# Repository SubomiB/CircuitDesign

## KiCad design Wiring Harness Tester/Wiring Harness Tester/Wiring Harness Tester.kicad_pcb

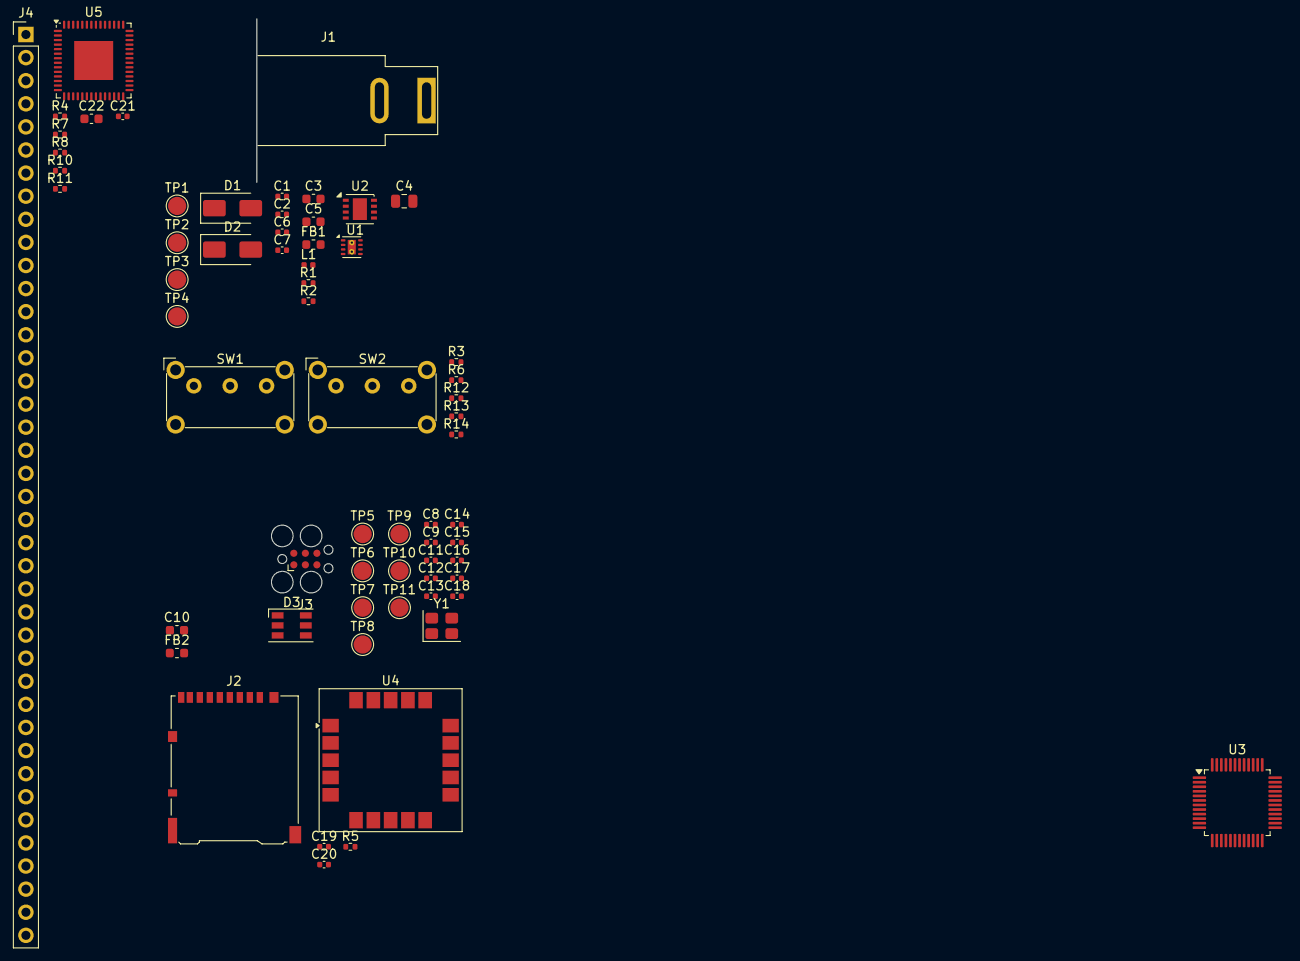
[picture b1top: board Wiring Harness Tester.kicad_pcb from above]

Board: 4 copper layers, 64 parts (0 on the bottom side), 79 nets, no tracks yet.

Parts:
C1, C2, C7, C16, C17: 1u; C_0402_1005Metric
C3: 10u; C_0603_1608Metric
C4: 22u; C_0805_2012Metric
C5, C10, C22: 4u7; C_0603_1608Metric
C6: 1n; C_0402_1005Metric
C8, C9: 10p; C_0402_1005Metric
C11, C12, C13, C14, C18, C19, C20, C21: 100n; C_0402_1005Metric
C15: 10n; C_0402_1005Metric
D1: SMAJ15A; D_SMA
D2: SS34; D_SMA
D3: CLX6F-FKC; LED_RGB_PLCC-6
FB1, FB2: 120R; L_0603_1608Metric
J1: 12V Jack; BarrelJack_SwitchcraftConxall_RAPC10U_Horizontal
J2: Micro_SD_Card_Det2; microSD_HC_Hirose_DM3AT-SF-PEJM5
J3: ST_Link; Tag-Connect_TC2030-IDC-FP_2x03_P1.27mm_Vertical
J4: Conn_01x40_Pin; PinHeader_1x40_P2.54mm_Vertical
L1: 2u2; L_0402_1005Metric
R1, R2: 100k; R_0402_1005Metric
R3, R5, R6: 10k; R_0402_1005Metric
R4, R7: 1k1; R_0402_1005Metric
R8: 2k; R_0402_1005Metric
R10, R11: 1k6; R_0402_1005Metric
R12: 75; R_0402_1005Metric
R13: 82; R_0402_1005Metric
R14: 62; R_0402_1005Metric
SW1, SW2: SW_SPDT; SW_E-Switch_EG1224_SPDT_Angled
TP1: T-GND; TestPoint_Pad_D2.0mm
TP2: T-12V; TestPoint_Pad_D2.0mm
TP3: T-5V; TestPoint_Pad_D2.0mm
TP4: T-3V3; TestPoint_Pad_D2.0mm
TP5, TP6: T-RX; TestPoint_Pad_D2.0mm
TP7: T-SCL; TestPoint_Pad_D2.0mm
TP8: T-SDA; TestPoint_Pad_D2.0mm
TP9: T-SCK; TestPoint_Pad_D2.0mm
TP10: T-MISO; TestPoint_Pad_D2.0mm
TP11: T-MOSI; TestPoint_Pad_D2.0mm
U1: TPS62163DSG; WSON-8-1EP_2x2mm_P0.5mm_EP0.9x1.6mm_ThermalVias
U2: MCP1727-3302xMF; DFN-8-1EP_3x3mm_P0.65mm_EP1.55x2.4mm
U3: STM32F103C8T6; LQFP-48_7x7mm_P0.5mm
U4: SAM-M8Q; ublox_SAM-M8Q
U5: PCA9506BS; QFN-56-1EP_8x8mm_P0.5mm_EP4.3x4.3mm
Y1: 8MHz; Crystal_SMD_3225-4Pin_3.2x2.5mm

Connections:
+3V3: C7.1, C10.1, C11.1, C12.1, C13.1, C14.1, C17.1, C19.1, C20.1, FB2.2, J2.4 (VDD), J3.1 (VCC), R2.2, R5.1, SW1.3 (C), SW2.3 (C), TP4.1, U2.7 (Sense), U2.8 (Vout), U3.1 (VBAT), U3.24 (VDD), U3.36 (VDD), U3.48 (VDD), U4.2 (VCC_IO), U4.3 (V_BCKP), U4.17 (VCC)
+5V: C4.1, C5.1, C21.1, C22.1, L1.2, R1.1, R4.1, R7.1, R8.1, R10.1, R11.1, TP3.1, U1.6 (VOS), U2.1 (Vin), U2.2 (Vin), U2.3 (~SHDN), U5.11 (V_{DD}), U5.39 (V_{DD})
+12V: C2.1, C3.1, FB1.2, TP2.1, U1.2 (VIN), U1.3 (EN)
+A3V3: C15.1, C16.1, FB2.1, U3.9 (VDDA)
/Microcontroller/SW_BOOT0: R6.1, SW2.2 (B)
BOOT0: R6.2, U3.44 (BOOT0)
Blue_LED: R12.2, U3.26 (PB13)
GND: C1.2, C2.2, C3.2, C4.2, C5.2, C6.2, C7.2, C8.2, C9.2, C10.2, C11.2, C12.2, C13.2, C14.2, C15.2, C16.2, C17.2, C18.1, C19.2, C20.2, C21.2, C22.2, D1.2 (A2), D3.1 (KB), D3.2 (KG), D3.3 (KR), J1.2, J2.6 (VSS), J2.11 (SHIELD), J3.5 (GND), SW1.1 (A), SW2.1 (A), TP1.1, U1.1 (PGND), U1.4 (AGND), U1.5 (FB), U2.4 (GND), U2.9 (GND), U3.8 (VSSA), U3.23 (VSS), U3.35 (VSS), U3.47 (VSS), U4.1 (GND), U4.4 (GND), U4.5 (GND), U4.6 (GND), U4.10 (GND), U4.11 (GND), U4.15 (GND), U4.16 (GND), U4.20 (GND), U5.4 (V_{SS}), U5.16 (V_{SS}), U5.20 (A0), U5.21 (A1), U5.22 (A2), U5.27 (V_{SS}), U5.32 (V_{SS}), U5.44 (V_{SS}), U5.55 (V_{SS}), U5.57 (V_{SS}), Y1.2, Y1.4
GPS_RESET: U3.32 (PA11), U4.18 (~RESET)
GPS_TIMEPULSE: U3.30 (PA9), U4.7 (TIMEPULSE)
Green_LED: R13.2, U3.27 (PB14)
I2C_SCL: R11.2, TP7.1, U3.45 (PB8), U5.51 (SCL)
I2C_SDA: R10.2, TP8.1, U3.46 (PB9), U5.50 (SDA)
MicroSD_CS: J2.2 (DAT3/CD), R5.2, U3.21 (PB10)
NRST: C18.2, J3.3 (~RESET), U3.7 (NRST)
unnamed: D1.1 (A1), D2.2 (A), J1.1
unnamed: C1.1, D2.1 (K), FB1.1
unnamed: D3.6 (AB), R12.1
unnamed: D3.5 (AG), R13.1
unnamed: D3.4 (AR), R14.1
unnamed: R3.1, SW1.2 (B)
unnamed: R1.2, U1.8 (PG)
unnamed: L1.1, U1.7 (SW)
unnamed: C6.1, U2.6 (Cdelay)
unnamed: R2.1, U2.5 (PWRGD)
OSC_In: C8.1, U3.5 (PD0), Y1.1
OSC_Out: C9.1, U3.6 (PD1), Y1.3
P1: J4.1, U5.52 (IO0_0)
P2: J4.2, U5.53 (IO0_1)
P3: J4.3, U5.54 (IO0_2)
P4: J4.4, U5.56 (IO0_3)
P5: J4.5, U5.1 (IO0_4)
P6: J4.6, U5.2 (IO0_5)
P7: J4.7, U5.3 (IO0_6)
P8: J4.8, U5.5 (IO0_7)
P9: J4.9, U5.6 (IO1_0)
P10: J4.10, U5.7 (IO1_1)
P11: J4.11, U5.8 (IO1_2)
P12: J4.12, U5.9 (IO1_3)
P13: J4.13, U5.10 (IO1_4)
P14: J4.14, U5.12 (IO1_5)
P15: J4.15, U5.13 (IO1_6)
P16: J4.16, U5.14 (IO1_7)
P17: J4.17, U5.15 (IO2_0)
P18: J4.18, U5.17 (IO2_1)
P19: J4.19, U5.18 (IO2_2)
P20: J4.20, U5.19 (IO2_3)
P21: J4.21, U5.24 (IO2_4)
P22: J4.22, U5.25 (IO2_5)
P23: J4.23, U5.26 (IO2_6)
P24: J4.24, U5.28 (IO2_7)
P25: J4.25, U5.29 (IO3_0)
P26: J4.26, U5.30 (IO3_1)
P27: J4.27, U5.31 (IO3_2)
P28: J4.28, U5.33 (IO3_3)
P29: J4.29, U5.34 (IO3_4)
P30: J4.30, U5.35 (IO3_5)
P31: J4.31, U5.36 (IO3_6)
P32: J4.32, U5.37 (IO3_7)
P33: J4.33, U5.38 (IO4_0)
P34: J4.34, U5.40 (IO4_1)
P35: J4.35, U5.41 (IO4_2)
P36: J4.36, U5.42 (IO4_3)
P37: J4.37, U5.43 (IO4_4)
P38: J4.38, U5.45 (IO4_5)
P39: J4.39, U5.46 (IO4_6)
P40: J4.40, U5.47 (IO4_7)
Red_LED: R14.2, U3.28 (PB15)
SPI_MISO: J2.7 (DAT0), TP10.1, U3.16 (PA6)
SPI_MOSI: J2.3 (CMD), TP11.1, U3.17 (PA7)
SPI_SCK: J2.5 (CLK), TP9.1, U3.15 (PA5)
SWD_CLK: J3.4 (SWCLK), U3.37 (PA14)
SWD_IO: J3.2 (SWDIO), U3.34 (PA13)
StartButtton: R3.2, U3.12 (PA2)
USART_RX: TP5.1, U3.43 (PB7), U4.14 (RXD)
USART_TX: TP6.1, U3.42 (PB6), U4.13 (TXD)
XPAN_INIT: R8.2, U3.39 (PB3), U5.48 (~INT)
XPAN_OE: R4.2, U5.23 (~OE)
XPAN_RESET: R7.2, U3.40 (PB4), U5.49 (~RESET)

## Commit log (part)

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2025-11-12 Add files via upload
    Reflectionless Filter For Load Pull Test Measurement Setups
2025-11-12 Add files via upload
    4-BIT ALU Hierarchical Design With LTSpice
2026-02-10 Save
